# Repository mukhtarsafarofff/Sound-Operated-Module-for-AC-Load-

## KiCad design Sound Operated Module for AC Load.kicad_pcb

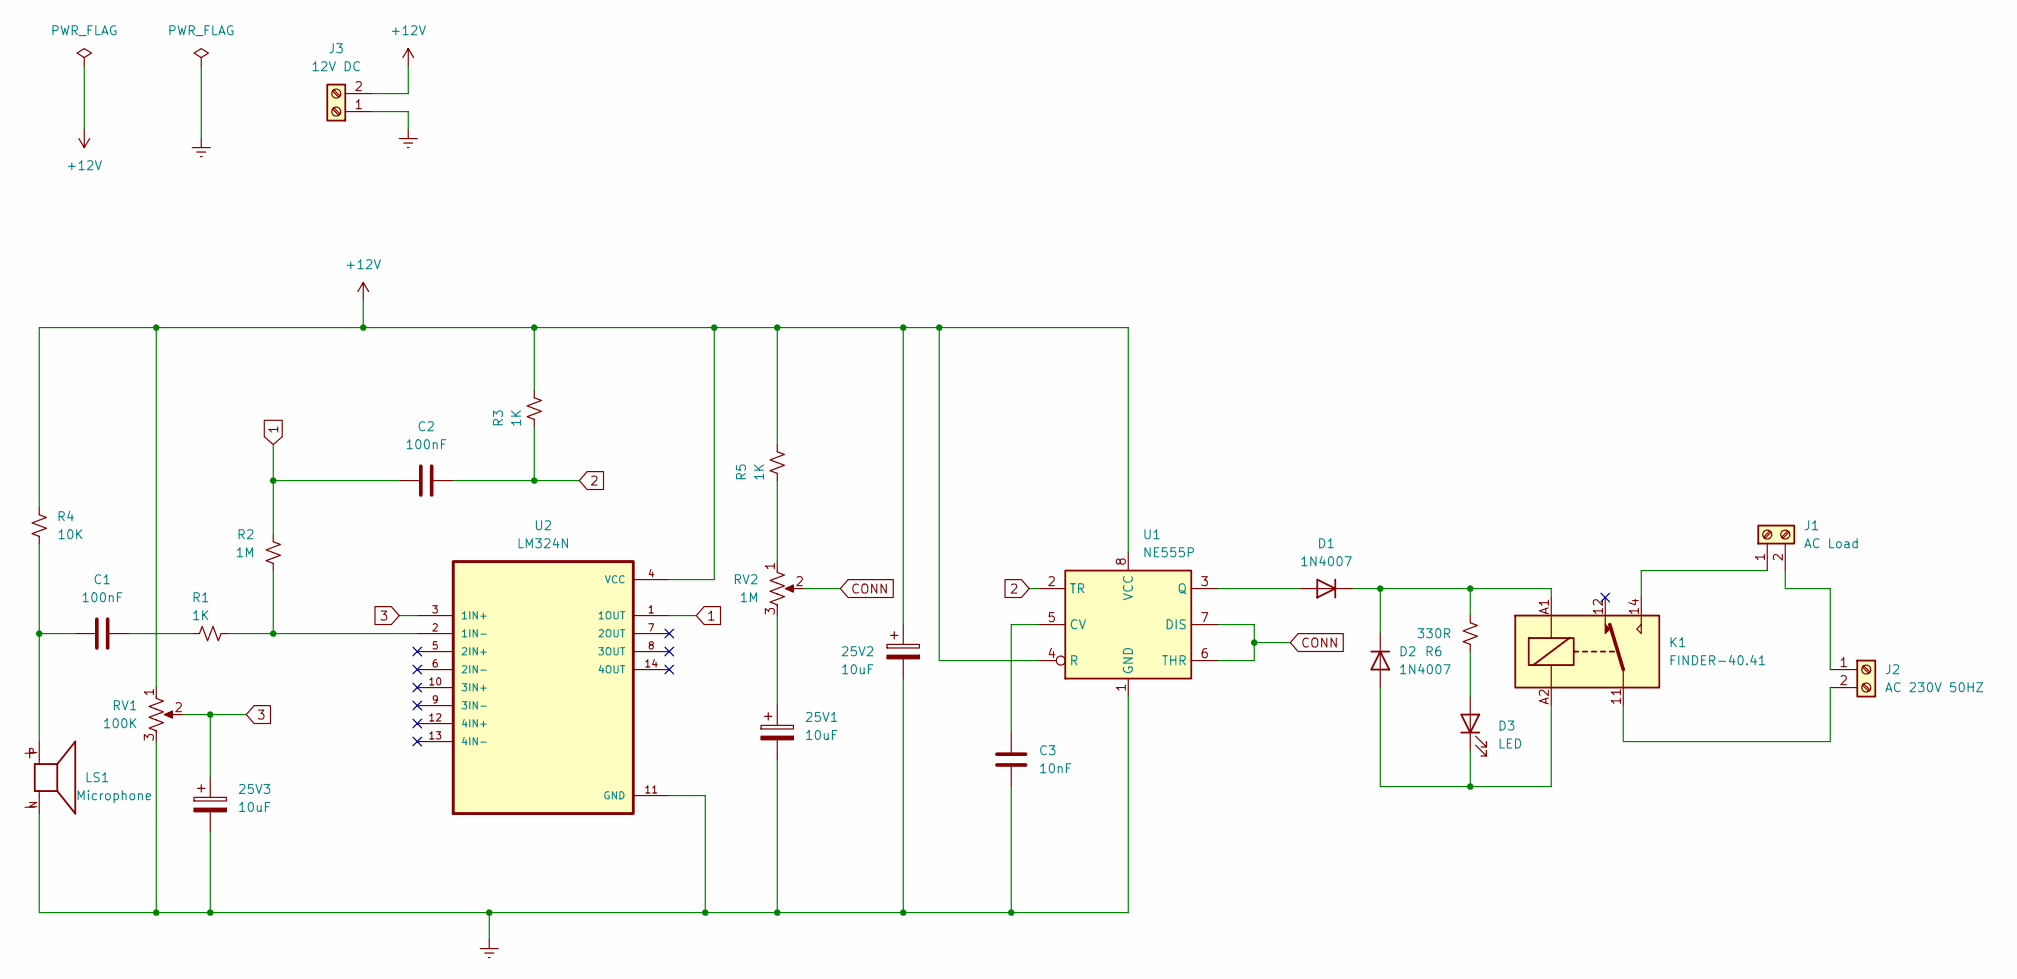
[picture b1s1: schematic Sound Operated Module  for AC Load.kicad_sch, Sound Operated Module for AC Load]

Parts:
25V1, 25V2, 25V3: 10uF; C_Disc_D7.5mm_W5.0mm_P7.50mm
C1, C2: 100nF; C_Disc_D7.5mm_W5.0mm_P7.50mm
C3: 10nF; C_Disc_D7.5mm_W5.0mm_P7.50mm
D1, D2: 1N4007; D_DO-41_SOD81_P10.16mm_Horizontal
D3: LED; LED_D5.0mm
J1: AC Load; TerminalBlock_bornier-2_P5.08mm
J2: AC 230V 50HZ; TerminalBlock_bornier-2_P5.08mm
J3: 12V DC; TerminalBlock_bornier-2_P5.08mm
K1: FINDER-40.41; Relay_SPDT_Finder_40.41
LS1: Microphone; MIC_POM-3042P-R; PARTREV B
R1, R3, R5: 1K; R_Axial_DIN0414_L11.9mm_D4.5mm_P15.24mm_Horizontal
R2: 1M; R_Axial_DIN0414_L11.9mm_D4.5mm_P15.24mm_Horizontal
R4: 10K; R_Axial_DIN0414_L11.9mm_D4.5mm_P15.24mm_Horizontal
R6: 330R; R_Axial_DIN0414_L11.9mm_D4.5mm_P15.24mm_Horizontal
RV1: 100K; Potentiometer_Vishay_148-149_Single_Horizontal
RV2: 1M; Potentiometer_Vishay_148-149_Single_Horizontal
U1: NE555P; DIP-8_W7.62mm
U2: LM324N; DIP-14_W7.62mm

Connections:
1: C2.1, R2.2, U2.1 (1OUT)
2: C2.2, R3.1, U1.2 (TR)
3: 25V3.1, RV1.2, U2.3 (1IN+)
+12V: 25V2.1, J3.2, R3.2, R4.2, R5.2, RV1.1, U1.4 (R), U1.8 (VCC), U2.4 (VCC)
CONN: RV2.2, U1.6 (THR), U1.7 (DIS)
Earth: 25V1.2, 25V2.2, 25V3.2, C3.1, J3.1, LS1.N, RV1.3, U1.1 (GND), U2.11 (GND)
unnamed: 25V1.1, RV2.3
unnamed: C1.1, LS1.P, R4.1
unnamed: C1.2, R1.1
unnamed: D1.2 (A), U1.3 (Q)
unnamed: D1.1 (K), D2.1 (K), K1.A1, R6.2
unnamed: D2.2 (A), D3.1 (K), K1.A2
unnamed: D3.2 (A), R6.1
unnamed: J1.1, K1.14
unnamed: J1.2, J2.1
unnamed: J2.2, K1.11
unnamed: R5.1, RV2.1
unnamed: C3.2, U1.5 (CV)
unnamed: R1.2, R2.1, U2.2 (1IN-)

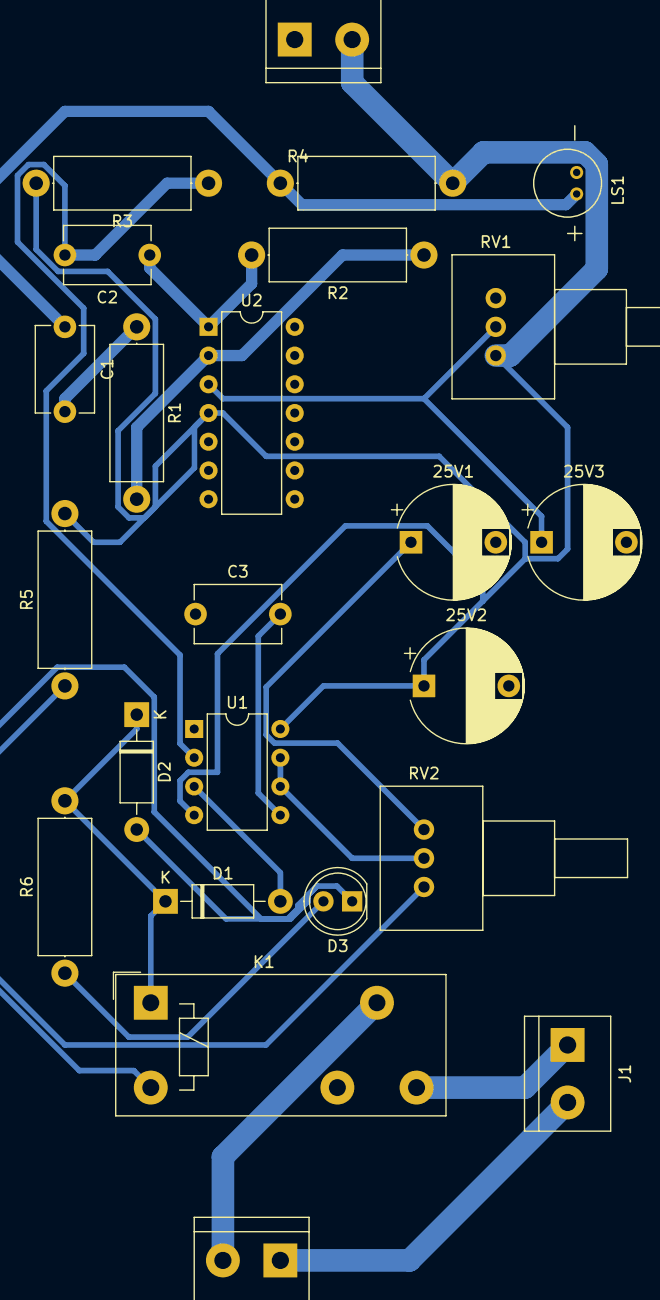
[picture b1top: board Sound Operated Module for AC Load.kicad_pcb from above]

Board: 2 copper layers, 24 parts (0 on the bottom side), 19 nets.

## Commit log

2024-03-24 Sound Operated Module for AC Load is accomplished
